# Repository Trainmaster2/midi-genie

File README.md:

MIDI Genie
==========
The MIDI Genie is an auxiliary APU for the Nintendo Entertainment System. The MIDI Genie is an add-on device that translates the audio output into MIDI. A custom PCB acts as a cartridge riser and holds the FPGA, level shifters, and other electronics to sniff NES bus traffic, process the data, and output MIDI. A USB serial command line offers control over the device's operations, including shifting the output by individual semitones and whole octaves.

The device sits between the cartridge and the console, much like the classic Game Genie devices. From there, it listens for instructions from the CPU to the built-in audio processor. Based on said instructions, the function of the APU is emulated, and live MIDI signals are generated to mimic the sounds the real APU would generate.

-----

This repo contains the KiCad project, Vivado project, and Vitis project for the device.

The Noise channel frequency calculations could use some work, and the DMC has yet to be researched or implemented.

More in-depth documentation will likely come at a future date.

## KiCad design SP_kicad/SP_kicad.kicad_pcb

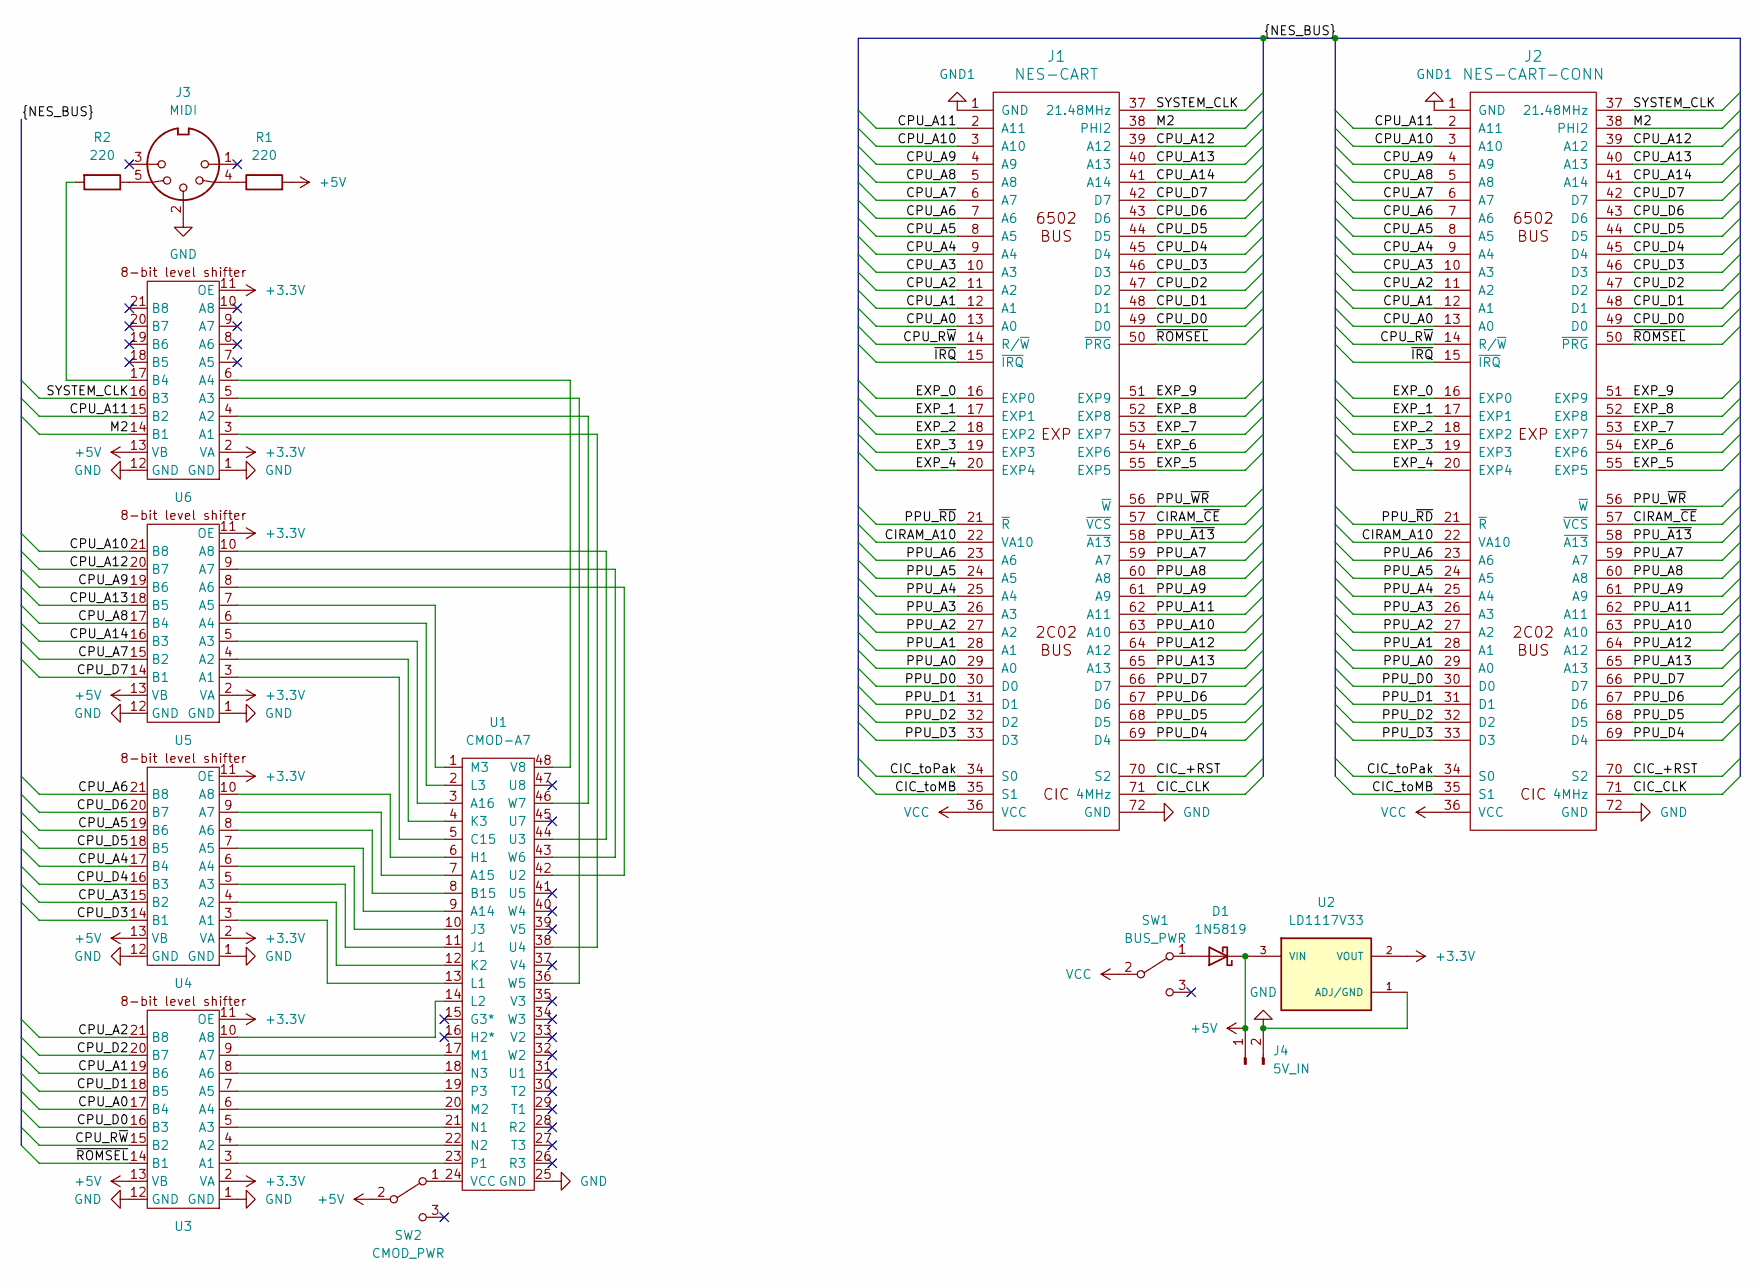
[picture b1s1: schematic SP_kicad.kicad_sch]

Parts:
D1: 1N5819; D_DO-41_SOD81_P10.16mm_Horizontal
J1: NES-CART; NES_CART_FINGERS
J2: NES-CART-CONN; NES-CART-CONN_1
J3: MIDI; MIDI_DIN5
J4: 5V_IN; PinHeader_1x02_P2.54mm_Vertical
R1, R2: 220; R_Axial_DIN0207_L6.3mm_D2.5mm_P10.16mm_Horizontal
SW1: BUS_PWR; PinHeader_1x03_P2.54mm_Vertical
SW2: CMOD_PWR; PinHeader_1x03_P2.54mm_Vertical
U1: CMOD-A7; CMOD-A7-DIP-48_W15.24mm
U2: LD1117V33; TO255P1020X450X1968-3; PARTREV 37
U3, U4, U5, U6: level-shifter

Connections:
+3.3V: U2.2 (VOUT), U3.2 (VA), U3.11 (OE), U4.2 (VA), U4.11 (OE), U5.2 (VA), U5.11 (OE), U6.2 (VA), U6.11 (OE)
+5V: D1.1 (K), J4.1, R1.2, SW2.2 (B), U2.3 (VIN), U3.13 (VB), U4.13 (VB), U5.13 (VB), U6.13 (VB)
/CIC_+RST: J1.70 (S2), J2.70 (S2)
/CIC_CLK: J1.71 (4MHz), J2.71 (4MHz)
/CIC_toMB: J1.35 (S1), J2.35 (S1)
/CIC_toPak: J1.34 (S0), J2.34 (S0)
/CIRAM_A10: J1.22 (VA10), J2.22 (VA10)
/CIRAM_~CE: J1.57 (~VCS), J2.57 (~VCS)
/CPU_A0: J1.13 (A0), J2.13 (A0), U3.17 (B4)
/CPU_A1: J1.12 (A1), J2.12 (A1), U3.19 (B6)
/CPU_A2: J1.11 (A2), J2.11 (A2), U3.21 (B8)
/CPU_A3: J1.10 (A3), J2.10 (A3), U4.15 (B2)
/CPU_A4: J1.9 (A4), J2.9 (A4), U4.17 (B4)
/CPU_A5: J1.8 (A5), J2.8 (A5), U4.19 (B6)
/CPU_A6: J1.7 (A6), J2.7 (A6), U4.21 (B8)
/CPU_A7: J1.6 (A7), J2.6 (A7), U5.15 (B2)
/CPU_A8: J1.5 (A8), J2.5 (A8), U5.17 (B4)
/CPU_A9: J1.4 (A9), J2.4 (A9), U5.19 (B6)
/CPU_A10: J1.3 (A10), J2.3 (A10), U5.21 (B8)
/CPU_A11: J1.2 (A11), J2.2 (A11), U6.15 (B2)
/CPU_A12: J1.39 (A12), J2.39 (A12), U5.20 (B7)
/CPU_A13: J1.40 (A13), J2.40 (A13), U5.18 (B5)
/CPU_A14: J1.41 (A14), J2.41 (A14), U5.16 (B3)
/CPU_D0: J1.49 (D0), J2.49 (D0), U3.16 (B3)
/CPU_D1: J1.48 (D1), J2.48 (D1), U3.18 (B5)
/CPU_D2: J1.47 (D2), J2.47 (D2), U3.20 (B7)
/CPU_D3: J1.46 (D3), J2.46 (D3), U4.14 (B1)
/CPU_D4: J1.45 (D4), J2.45 (D4), U4.16 (B3)
/CPU_D5: J1.44 (D5), J2.44 (D5), U4.18 (B5)
/CPU_D6: J1.43 (D6), J2.43 (D6), U4.20 (B7)
/CPU_D7: J1.42 (D7), J2.42 (D7), U5.14 (B1)
/CPU_R~W: J1.14 (R/~W), J2.14 (R/~W), U3.15 (B2)
/EXP_0: J1.16 (EXP0), J2.16 (EXP0)
/EXP_1: J1.17 (EXP1), J2.17 (EXP1)
/EXP_2: J1.18 (EXP2), J2.18 (EXP2)
/EXP_3: J1.19 (EXP3), J2.19 (EXP3)
/EXP_4: J1.20 (EXP4), J2.20 (EXP4)
/EXP_5: J1.55 (EXP5), J2.55 (EXP5)
/EXP_6: J1.54 (EXP6), J2.54 (EXP6)
/EXP_7: J1.53 (EXP7), J2.53 (EXP7)
/EXP_8: J1.52 (EXP8), J2.52 (EXP8)
/EXP_9: J1.51 (EXP9), J2.51 (EXP9)
/M2: J1.38 (PHI2), J2.38 (PHI2), U6.14 (B1)
/PPU_A0: J1.29 (A0), J2.29 (A0)
/PPU_A1: J1.28 (A1), J2.28 (A1)
/PPU_A2: J1.27 (A2), J2.27 (A2)
/PPU_A3: J1.26 (A3), J2.26 (A3)
/PPU_A4: J1.25 (A4), J2.25 (A4)
/PPU_A5: J1.24 (A5), J2.24 (A5)
/PPU_A6: J1.23 (A6), J2.23 (A6)
/PPU_A7: J1.59 (A7), J2.59 (A7)
/PPU_A8: J1.60 (A8), J2.60 (A8)
/PPU_A9: J1.61 (A9), J2.61 (A9)
/PPU_A10: J1.63 (A10), J2.63 (A10)
/PPU_A11: J1.62 (A11), J2.62 (A11)
/PPU_A12: J1.64 (A12), J2.64 (A12)
/PPU_A13: J1.65 (A13), J2.65 (A13)
/PPU_D0: J1.30 (D0), J2.30 (D0)
/PPU_D1: J1.31 (D1), J2.31 (D1)
/PPU_D2: J1.32 (D2), J2.32 (D2)
/PPU_D3: J1.33 (D3), J2.33 (D3)
/PPU_D4: J1.69 (D4), J2.69 (D4)
/PPU_D5: J1.68 (D5), J2.68 (D5)
/PPU_D6: J1.67 (D6), J2.67 (D6)
/PPU_D7: J1.66 (D7), J2.66 (D7)
/PPU_~A13: J1.58 (~A13), J2.58 (~A13)
/PPU_~RD: J1.21 (~R), J2.21 (~R)
/PPU_~WR: J1.56 (~W), J2.56 (~W)
/SYSTEM_CLK: J1.37 (21.48MHz), J2.37 (21.48MHz), U6.16 (B3)
/~IRQ: J1.15 (~IRQ), J2.15 (~IRQ)
/~ROMSEL: J1.50 (~PRG), J2.50 (~PRG), U3.14 (B1)
GND: J1.72 (GND), J2.72 (GND), J3.2, J4.2, U1.25 (GND), U2.1 (ADJ/GND), U3.1 (GND), U3.12 (GND), U4.1 (GND), U4.12 (GND), U5.1 (GND), U5.12 (GND), U6.1 (GND), U6.12 (GND)
GND1: J1.1 (GND), J2.1 (GND)
unnamed: D1.2 (A), SW1.1 (A)
unnamed: J3.4, R1.1
unnamed: J3.5, R2.1
unnamed: SW2.1 (A), U1.24 (VCC)
unnamed: U1.9 (A14), U4.7 (A5)
unnamed: U1.7 (A15), U4.9 (A7)
unnamed: U1.3 (A16), U5.5 (A3)
unnamed: U1.8 (B15), U4.8 (A6)
unnamed: U1.5 (C15), U5.3 (A1)
unnamed: U1.6 (H1), U4.10 (A8)
unnamed: U1.11 (J1), U4.5 (A3)
unnamed: U1.10 (J3), U4.6 (A4)
unnamed: U1.12 (K2), U4.4 (A2)
unnamed: U1.4 (K3), U5.4 (A2)
unnamed: U1.13 (L1), U4.3 (A1)
unnamed: U1.14 (L2), U3.10 (A8)
unnamed: U1.2 (L3), U5.6 (A4)
unnamed: U1.17 (M1), U3.9 (A7)
unnamed: U1.20 (M2), U3.6 (A4)
unnamed: U1.1 (M3), U5.7 (A5)
unnamed: U1.21 (N1), U3.5 (A3)
unnamed: U1.22 (N2), U3.4 (A2)
unnamed: U1.18 (N3), U3.8 (A6)
unnamed: U1.23 (P1), U3.3 (A1)
unnamed: U1.19 (P3), U3.7 (A5)
unnamed: U1.42 (U2), U5.8 (A6)
unnamed: U1.44 (U3), U5.10 (A8)
unnamed: U1.48 (V8), U6.6 (A4)
unnamed: U1.43 (W6), U5.9 (A7)
unnamed: U1.46 (W7), U6.4 (A2)
unnamed: R2.2, U6.17 (B4)
VCC: J1.36 (VCC), J2.36 (VCC), SW1.2 (B)

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
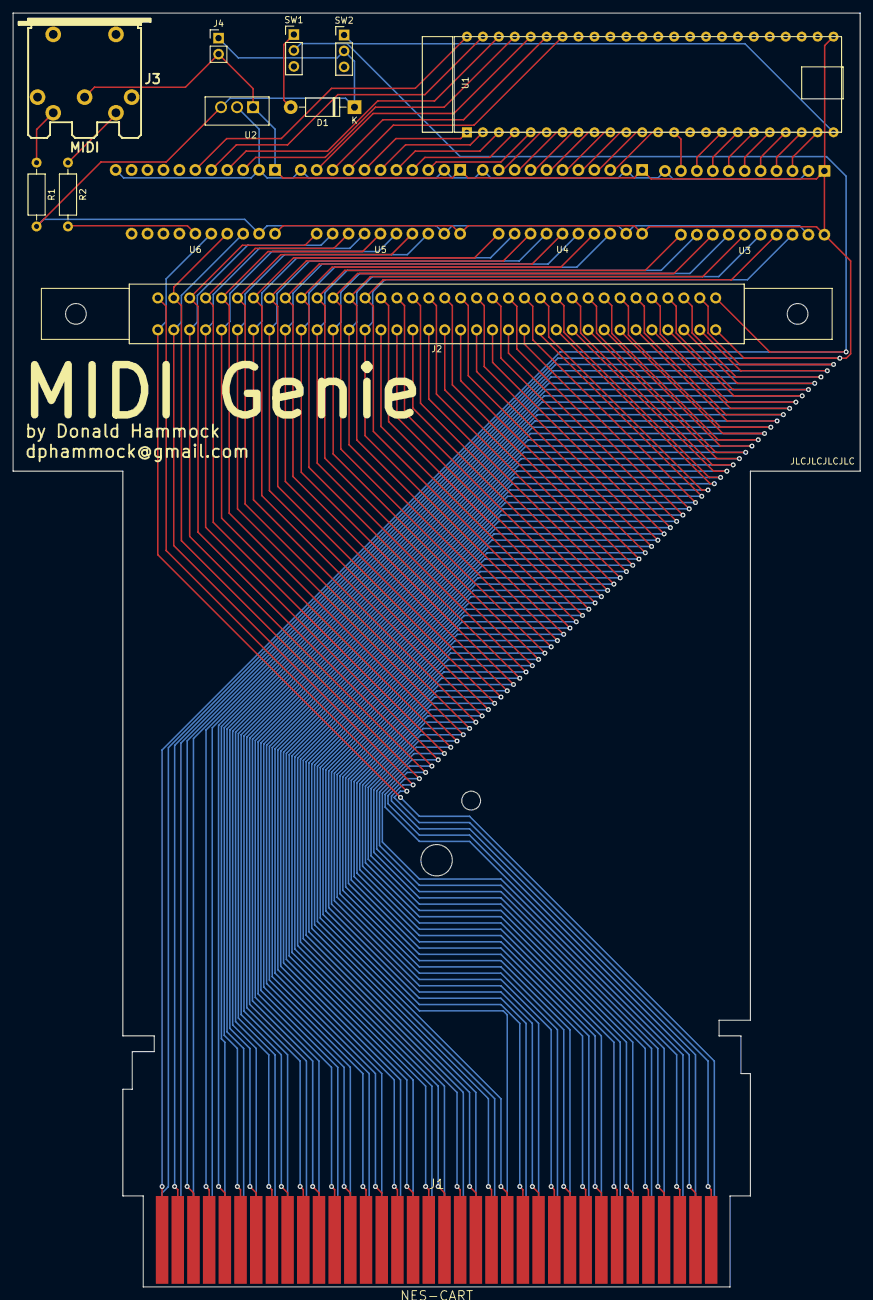
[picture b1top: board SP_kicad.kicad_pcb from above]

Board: 2 copper layers, 135.0 x 203.0 mm, 15 parts (0 on the bottom side), 107 nets.

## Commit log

2023-09-13 Created PCB
2023-09-13 Update level shifter placement
2023-09-13 Created Vivado project
2023-09-15 Implemented (broken) NES reset detector
2023-11-04 Implemented APU records and registers
    Also a new attempt at reset detection and moved M2 and System_Clk
2023-11-05 More reset detection attempts
2023-11-05 Added reset to APU registers
2023-11-06 Created beginnings of APU block
2023-11-13 Updated M2 and SYSTEM_CLK placement
2023-12-26 Syncthing to Linux
2024-01-08 Algorithm testing
2024-01-09 Added Microblaze processor
2024-01-09 Created Vitis project
2024-01-09 Added 3D printing files
2024-01-09 Added calc.cpp
2024-01-09 Enabled multiplier, divider, and floating point
2024-01-09 Switched calc.h to macros
2024-01-10 Added MIDI output
    fifo_transmitter.vhd pulled from previous test project
    axi_fifo_writer.vhd modified from previous test project (AXI implementation based on links at top of file)
2024-01-10 Fixed transmitter and added midi.h
2024-01-11 Increased heap and clamped MIDI calculations
2024-01-11 Bit-field testing
2024-01-12 Implemented axi_fifo_reader
2024-01-12 Added interrupts and created apu.cpp
2024-01-17 Define-based config testing
2024-01-18 Connected APU to processor
2024-01-18 Switched to one message per channel
2024-01-18 Implemented reset_manager
    Also added hierarchies, could no longer update hardware in Vitis, attempted to force it to work, decided I didn't want hierarchies, and had to recreate the Vitis project anyway.
2024-02-11 APU frame counter, pulse length counter, and additional software config
2024-02-13 Optimizations and bug fix
2024-02-14 Implemented pulse channel envelope
2024-02-14 Implemented sweep and fixed length counter load
    There seems to be issues with the Monopoly menu music now. Needs to be investigated.
2024-02-14 Fixed sweep shifting
2024-02-14 Increased UART baud from 9600 to 230400
    Mostly fixes slowdown from APU debugging messages
2024-02-23 Implemented triangle channel
2024-02-23 Created noise calculations
    Since noise is pseudo-random, it can't be calculated with a simple formula. Mode 0 has one unique cycle covering all values, while mode 1 has 353 unique cycles depending on when it switches. By calcu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
2024-03-10 Initial Noise implementation
    Most of the implementation seems complete, but frequency calculations need to be reworked. Noise disabled at apu writer.
2024-03-10 Created DMC groundwork
2024-05-08 Moved Kicad footprints into project
2024-05-10 Added controllable APU FIFO writer
2024-05-14 Added UART interface
2024-05-24 Implemented octave and semitone shifting
2024-06-03 Finished Noise channel calculations
    The frequency calculations could use a bit of fine tuning, but work well enough.
2024-06-13 Public release
